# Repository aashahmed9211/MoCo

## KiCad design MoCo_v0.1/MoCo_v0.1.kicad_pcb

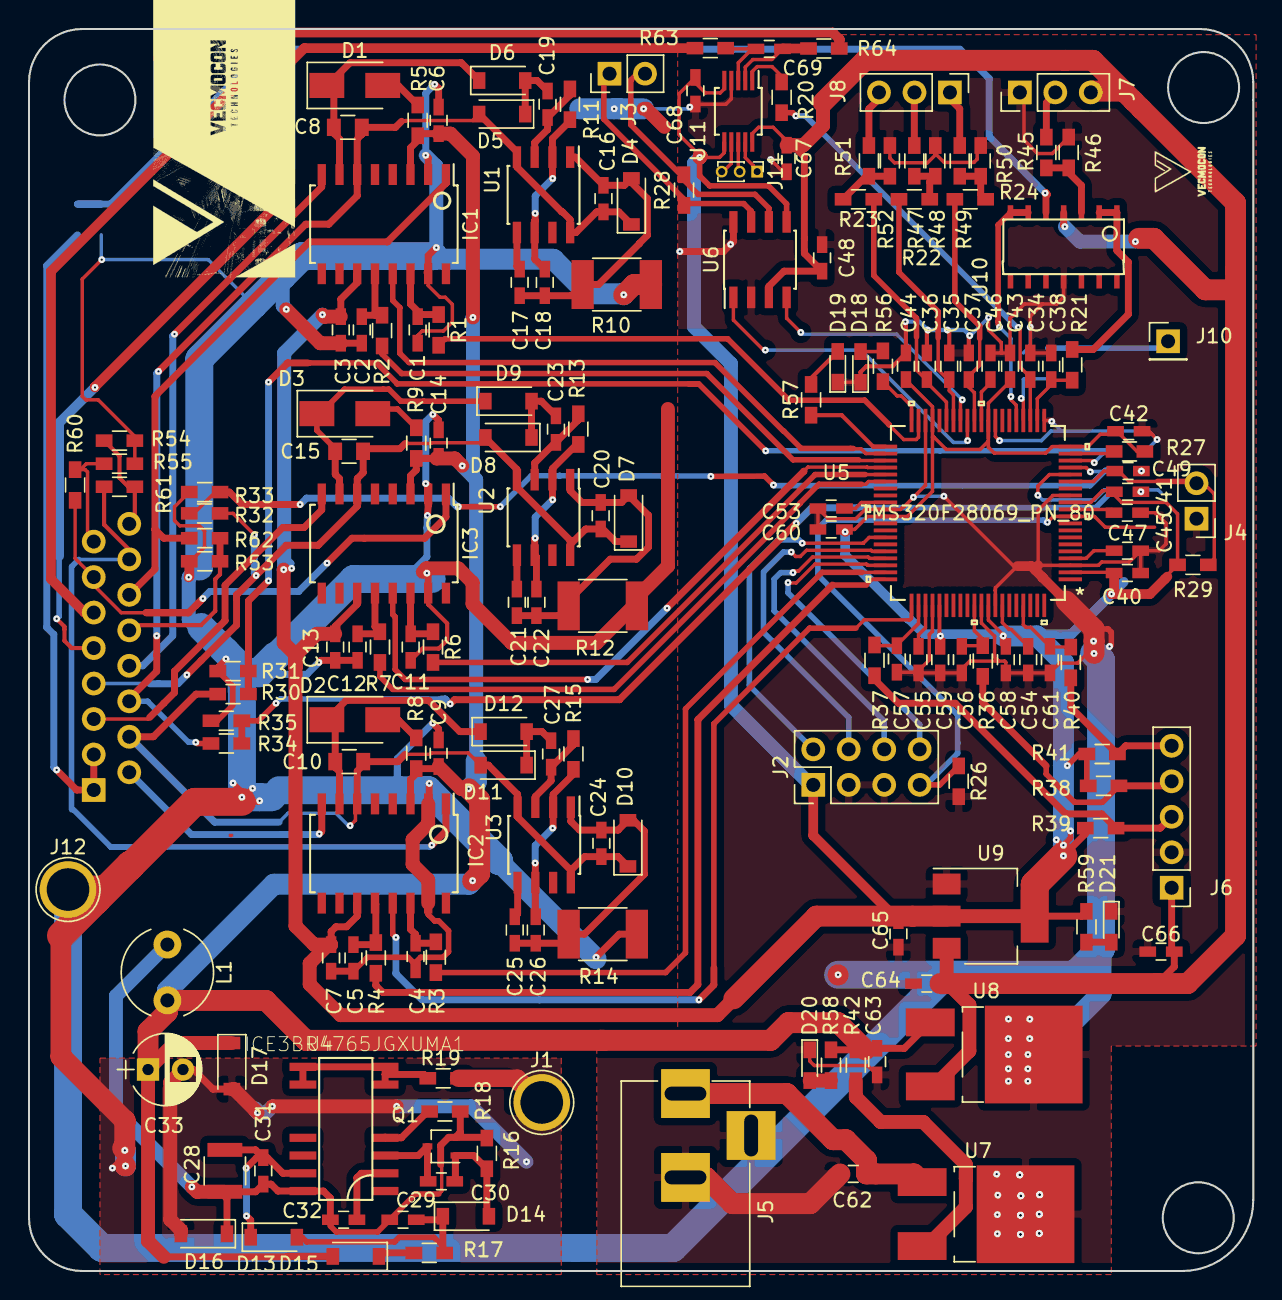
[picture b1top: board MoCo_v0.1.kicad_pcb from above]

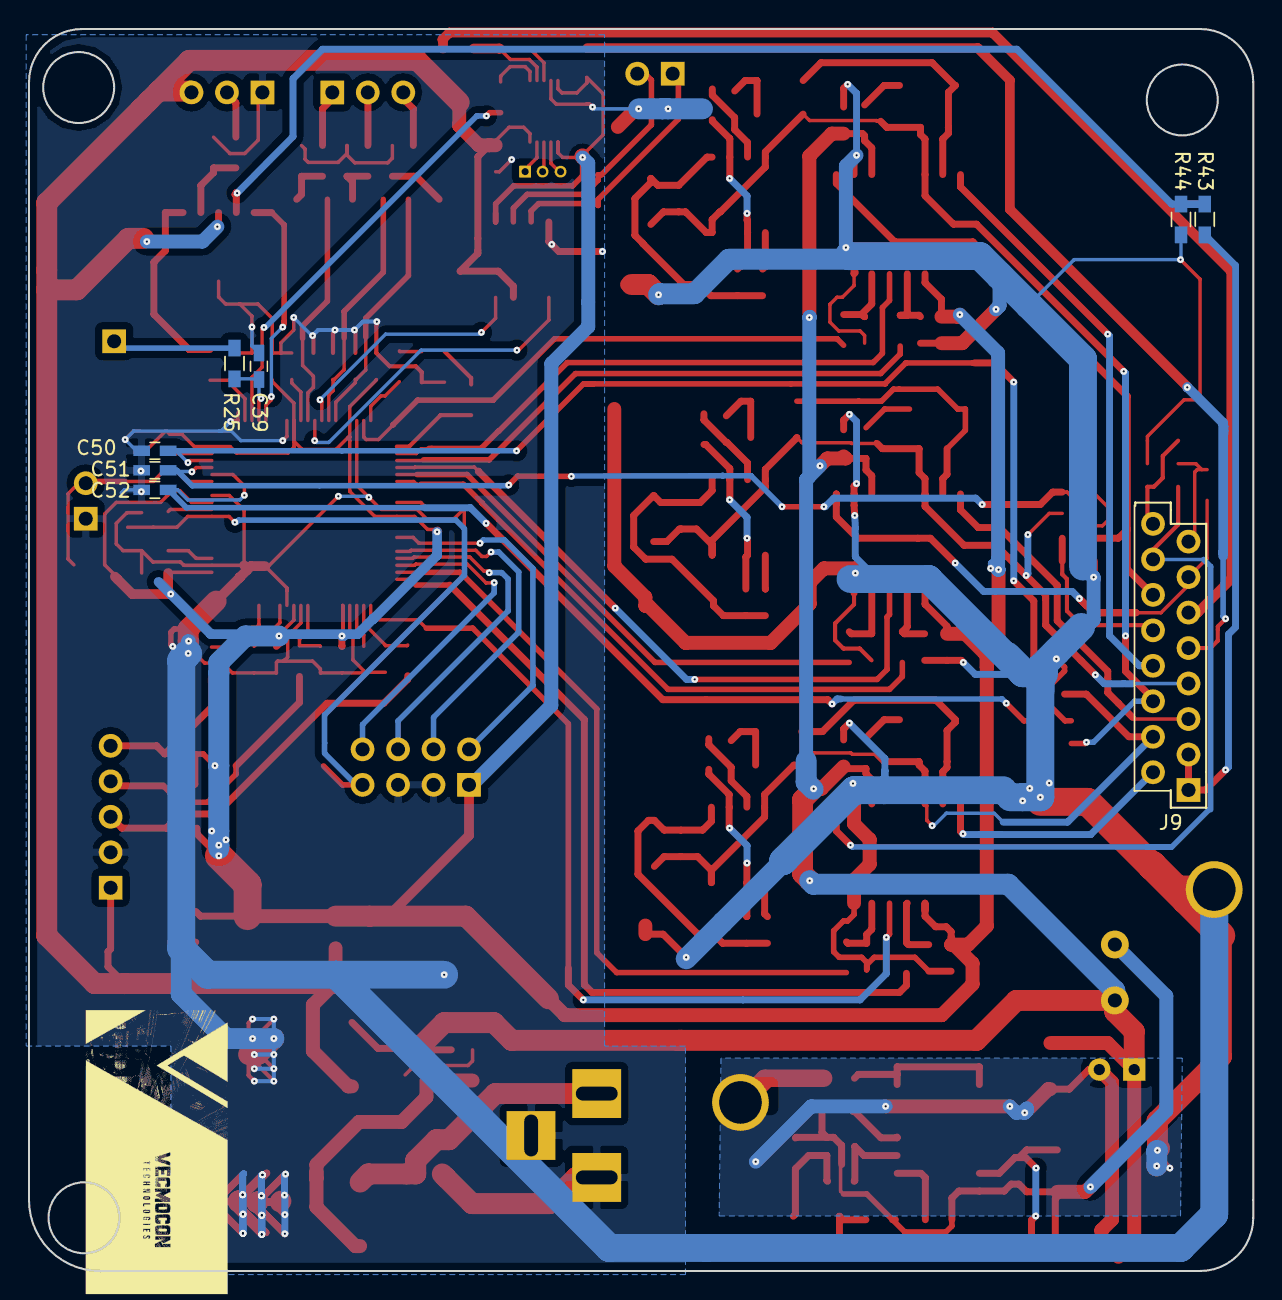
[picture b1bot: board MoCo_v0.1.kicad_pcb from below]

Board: 2 copper layers, 87.6 x 88.9 mm, 182 parts (8 on the bottom side), 123 nets.

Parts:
C1, C2, C4, C5, C11, C12, C19, C23, C27: 10nf; C_0603_HandSoldering
C3, C6, C7, C9, C13, C14, C62, C63: 1uf; C_0603_HandSoldering
C8, C10, C15: 10uf; C_0805
C16, C17, C20, C21, C24, C25, C30, C31, C64, C65, C66: 100nf; C_0603_HandSoldering
C18, C22, C26: 1nf; C_0603_HandSoldering
C28: 10uf; C_1210
C29, C32: 470nf; C_0603_HandSoldering
C33: CP1; CP_Radial_D5.0mm_P2.50mm
C34, C35, C36, C37, C38, C39, C42, C44, C45, C46, C49, C50, C51, C52, C53, C54, C55: 2.2uF; C_0603_HandSoldering
C40, C41, C43, C47, C56, C57, C58, C59, C60, C61: 1.2uF; C_0603_HandSoldering
C48: 10uF; C_0603_HandSoldering
C67, C68, C69: 100NF; C_0603_HandSoldering
D1, D2, D3: D; D_SMA
D4, D7, D10, D13, D14: D_Zener; D_SOD-123
D5, D6, D8, D9, D11, D12, D15, D16: D; D_SOD-123
D17: D_Zener_18v; D_SOD-123
D18, D19, D20, D21: LED; LED_0603_HandSoldering
IC1, IC2, IC3: AUIRS2110S; SOIC-16W_5.3x10.2mm_Pitch1.27mm
J1: BUCK_IN; 1pin
J2: Conn_02x04_Odd_Even; Pin_Header_Straight_2x04_Pitch2.54mm
J3: CAN; Pin_Header_Straight_1x02_Pitch2.54mm
J4: NTC; Pin_Header_Straight_1x02_Pitch2.54mm
J5: Jack-DC; BARREL_JACK
J6: Conn_01x05; Pin_Header_Straight_1x05_Pitch2.54mm
J7, J8: Conn_01x03; Pin_Header_Straight_1x03_Pitch2.54mm
J9: Conn_02x08_Odd_Even; Pin_Header_Straight_2x08_Pitch2.54mm
J10: Conn_01x01; Pin_Header_Straight_1x01_Pitch2.54mm
J11: Conn_01x03; Pin_Header_Straight_1x03_Pitch1.00mm
J12: Conn_01x01; 1pin
L1: 1mh; L_Radial_D6.0mm_P4.00mm
Q1: -; SOT-323_SC-70
R1, R2, R3, R4, R5, R6, R7, R8, R9, R17: 10R; R_0603_HandSoldering
R10, R12, R14: 10k; R_1812
R11, R13, R15: 100k; R_0603_HandSoldering
R16: 1k; R_0603_HandSoldering
R18: 2.2R; R_0603_HandSoldering
R19, R29, R30, R31, R32, R33, R34, R35, R36, R37, R38, R39, R40, R41, R49, R50, R51, R52, R58, R59, R63, R64: R; R_0603_HandSoldering
R20, R21, R22, R23, R24, R25, R28: 120; R_0603_HandSoldering
R26, R60, R61, R62: 10K; R_0603_HandSoldering
R27, R42: 0; R_0603_HandSoldering
R43: 68k; R_0603_HandSoldering
R44, R45: 2.2k; R_0603_HandSoldering
R46, R48: 3.3k; R_0603_HandSoldering
R47: 12k; R_0603_HandSoldering
R53, R54, R55: 21k; R_0603_HandSoldering
R56, R57: 4.7k; R_0603_HandSoldering
U1, U2, U3: ICM7555; SOIC-8_3.9x4.9mm_Pitch1.27mm
U4: ICE3BR4765JGXUMA1; SOIC127P1032X265-16N
U5: TMS320F28069_PN_80; TMS320F28069PNT
U6: TJA1042T/3; SOIC-8_3.9x4.9mm_Pitch1.27mm
U7: LM7812CT_LTB; TO-252-2_Rectifier
U8: LM7805CT_LTB; TO-252-2_Rectifier
U9: LD1117S33CTR; SOT-223
U10: LM324AMX/NOPB; lm324dt so14
U11: INA2181A1; MSOP-10_3x3mm_Pitch0.5mm

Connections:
+3V3: C3.1, C7.1, C13.1, C40.1, C41.1, C42.1, C43.2, C44.1, C58.1, C59.2, C60.2, C65.1, C68.2, IC1.11, IC2.11, IC3.11, J2.1, R27.2, R29.1, R38.2, R39.2, R41.2, R59.1, U5.2, U5.12, U5.20, U5.29, U5.37, U5.51, U5.65, U5.72, U6.5, U9.2, U9.4, U11.5, U11.6
+5V: C48.2, C64.1, C66.2, C67.1, J6.1, J7.3, U6.3, U8.3, U9.3, U10.4, U11.10
+12V: C6.2, C9.2, C14.2, C33.1, C63.1, D15.2, D17.1, IC1.3, IC2.3, IC3.3, L1.2, R5.2, R8.2, R9.2, R42.1, R58.1, U8.1
/ChargePump/PH1: C10.1, C24.1, D10.1, D11.2, IC2.6, J9.4, R30.1, U3.4, U3.8
/ChargePump/PH2: C15.1, C20.1, D7.1, D8.2, IC3.6, J9.7, R32.1, U2.4, U2.8
/ChargePump/PH3: C8.1, C16.1, D4.1, D5.2, IC1.6, J9.6, R34.1, U1.4, U1.8
/ChargePump/VB1: C10.2, D2.1, D12.1, IC2.7
/ChargePump/VB2: C15.2, D3.1, D9.1, IC3.7
/ChargePump/VB3: C8.2, D1.1, D6.1, IC1.7
/MCU/BRAKE: R22.2, R47.2, R48.1
/MCU/BUS_SENSE: U5.25, U10.6, U10.7
/MCU/CURRENT_SENSE1: R20.2, U11.1
/MCU/CURRENT_SENSE2: J10.1, R25.2
/MCU/HALL_A: J6.3, R37.1, R39.1
/MCU/HALL_B: J6.4, R36.1, R38.1
/MCU/HALL_C: J6.5, R40.1, R41.1
/MCU/HIN1: R4.2, U5.60
/MCU/HIN2: R7.2, U5.46
/MCU/HIN3: R2.2, U5.43
/MCU/LIN1: R3.2, U5.59
/MCU/LIN2: R6.2, U5.45
/MCU/LIN3: R1.2, U5.39
/MCU/MODES: R24.2, R49.2, R50.1
/MCU/PH1_V: C50.2, R30.2, R31.1, U5.18
/MCU/PH2_V: C51.2, R32.2, R33.1, U5.17
/MCU/PH3_V: C52.2, R34.2, R35.1, U5.16
/MCU/REVERSE: R23.2, R51.2, R52.1
/MCU/RXD: U5.33, U6.4
/MCU/SD1: IC2.13, U5.61
/MCU/SD2: IC3.13, U5.44
/MCU/SD3: IC1.13, U5.42
/MCU/TCK: J2.2, U5.54
/MCU/TDI: J2.6, U5.57
/MCU/TDO: J2.4, U5.56
/MCU/TEMP_MOS: C49.2, J4.2, R29.2, U5.15
/MCU/THROTTLE: R21.2, U10.1, U10.2
/MCU/TMS: J2.8, U5.58
/MCU/TRST: J2.7, R26.1, U5.10
/MCU/TXD: U5.32, U6.1
/connector/B: R43.2, R44.1, U10.5
/connector/BRK: J8.2, R47.1
/connector/HO1: IC2.8, J9.2
/connector/HO2: IC3.8, J9.5
/connector/HO3: IC1.8, J9.8
/connector/LO1: IC2.1, J9.14, R61.1
/connector/LO2: IC3.1, J9.13, R60.2
/connector/LO3: IC1.1, J9.12, R62.1
/connector/MOD: J8.1, R49.1
/connector/PH1_Source: J9.16, R54.1, R61.2
/connector/PH2_Source: J9.15, R55.1, R60.1
/connector/PH3_Source: J9.10, R53.1, R62.2
/connector/RVRS: J8.3, R51.1
/connector/SHUNT+: J9.9, R63.2
/connector/SHUNT-: J9.11, R64.2
/connector/TH: R45.2, R46.1, U10.3
/connector/THR: J7.2, R45.1
/connector/VBAT: J9.1, J9.3, R43.1
GND: C1.2, C2.2, C3.2, C4.2, C5.2, C6.1, C7.2, C9.1, C11.2, C12.2, C13.2, C14.1, C33.2, C34.1, C35.1, C36.1, C37.1, C38.2, C39.1, C40.2, C41.2, C42.2, C43.1, C44.2, C45.2, C46.2, C47.2, C48.1, C49.1, C50.1, C51.1, C52.1, C53.2, C54.2, C55.2, C56.1, C57.1, C58.2, C59.1, C60.1, C61.1, C62.2, C63.2, C64.2, C65.2, C66.1, C67.2, C68.1, D16.2, D17.2, D18.1, D19.1, D20.1, D21.1, IC1.2, IC1.15, IC2.2, IC2.15, IC3.2, IC3.15, J2.3, J2.5, J4.1, J5.2, J5.3, J6.2, J7.1, J12.1, R10.2, R12.2, R14.2, R26.2, R31.2, R33.2, R35.2, R44.2, R46.2, R48.2, R50.2, R52.2, R53.2, R54.2, R55.2, U5.3, U5.13, U5.21, U5.28, U5.38, U5.50, U5.64, U5.71, U5.73, U6.2, U6.8, U7.2, U8.2, U9.1, U10.11, U11.4
unnamed: C1.1, IC1.14, R1.1
unnamed: C2.1, IC1.12, R2.1
unnamed: C4.1, IC2.14, R3.1
unnamed: C5.1, IC2.12, R4.1
unnamed: C11.1, IC3.14, R6.1
unnamed: C12.1, IC3.12, R7.1
unnamed: C16.2, C17.2, C18.2, D4.2, R10.1, U1.1
unnamed: C17.1, U1.5
unnamed: C18.1, R11.2, U1.2, U1.6
unnamed: C19.1, D5.1, D6.2
unnamed: C19.2, R11.1, U1.3
unnamed: C20.2, C21.2, C22.2, D7.2, R12.1, U2.1
unnamed: C21.1, U2.5
unnamed: C22.1, R13.2, U2.2, U2.6
unnamed: C23.1, D8.1, D9.2
unnamed: C23.2, R13.1, U2.3
unnamed: C24.2, C25.2, C26.2, D10.2, R14.1, U3.1
unnamed: C25.1, U3.5
unnamed: C26.1, R15.2, U3.2, U3.6
unnamed: C27.1, D11.1, D12.2
unnamed: C27.2, R15.1, U3.3
unnamed: C28.1, C31.1, D13.1, U4.11
unnamed: C28.2, C29.2, C31.2, C32.2, D16.1, L1.1, Q1.2, R16.2, R18.2, U4.12
unnamed: C29.1, D13.2, D14.1, R17.2
unnamed: C30.1, Q1.3, U4.3
unnamed: C30.2, D14.2, Q1.1, R16.1
unnamed: C32.1, U4.2
unnamed: C34.2, R20.1, U5.23
unnamed: C35.2, R22.1, U5.34
unnamed: C36.2, R23.1, U5.35
unnamed: C37.2, R24.1, U5.31
unnamed: C38.1, R21.1, U5.22
unnamed: C39.2, R25.1, U5.24
unnamed: C45.1, U5.11
unnamed: C46.1, U5.30
unnamed: C47.1, U5.4
unnamed: C53.1, U5.49
unnamed: C54.1, U5.74
unnamed: C55.1, U5.63
unnamed: C56.2, R36.2, U5.70
unnamed: C57.2, R37.2, U5.62
unnamed: C61.2, R40.2, U5.77
unnamed: C62.1, J5.1, U7.1
unnamed: C69.1, R63.1, U11.3
unnamed: C69.2, R64.1, U11.2
unnamed: D1.2, R5.1
unnamed: D2.2, R8.1
unnamed: D3.2, R9.1
unnamed: D15.1, R17.1
unnamed: D18.2, R56.2
unnamed: D19.2, R57.2
unnamed: D20.2, R58.2
unnamed: D21.2, R59.2
unnamed: J1.1, R19.1
unnamed: J3.1, R28.2, U6.7
unnamed: J3.2, R28.1, U6.6
unnamed: J11.1, U11.9
unnamed: J11.2, U11.8
unnamed: J11.3, U11.7
unnamed: R18.1, U4.4
unnamed: R19.2, U4.5, U4.6, U4.7, U4.8
unnamed: R27.1, U5.19
unnamed: R42.2, U7.3
unnamed: R56.1, U5.40
unnamed: R57.1, U5.41

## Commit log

2018-06-09 creating index file
2018-06-09 add this
2018-07-25 final

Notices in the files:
parts and their libraries:
Copyright 2016 Accelerated Designs. All rights reserved.
